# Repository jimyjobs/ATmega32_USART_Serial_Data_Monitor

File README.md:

# ATmega32 USART Serial Data Monitor System

## Overview

This project was completed for CT_321_PBL_04 as an exercise in serial communication using the ATmega32 microcontroller.

The idea behind the project was simple: monitor the state of multiple push buttons and report their status through a USART connection. In addition to transmitting data, the microcontroller was also required to receive commands from a serial terminal and respond appropriately.

The project started with a SimulIDE prototype to verify the firmware logic before moving to schematic capture and PCB design in KiCad.

## Development Process

The firmware was written in C using MPLAB XC8. USART communication was configured for 9600 baud at an 8 MHz system clock. Three push buttons were connected as digital inputs and two LEDs were used to provide visual feedback during operation.

Once the firmware was working correctly in simulation, a custom PCB was designed in KiCad. The design includes:

* ATmega32 DIP package
* 8 MHz crystal oscillator
* Crystal load capacitors
* Decoupling capacitors
* Three push-button inputs
* Two indicator LEDs
* USART header for serial communication

After routing was completed, the board was checked using KiCad's Design Rule Checker (DRC) and all reported issues were resolved before generating the manufacturing files.

## Functional Testing

Testing was performed in SimulIDE using the SerialTerm-32 terminal.

### Switch Monitoring

Each switch press generated the expected message on the serial terminal.

Example:

SW1 PRESSED

SW2 PRESSED

SW3 PRESSED

### Echo Function

To verify bidirectional communication, text entered into the serial terminal was echoed back by the microcontroller.

Example:

Input:
hello

Output:
hello

### STATUS Command

A STATUS command was added to display the current state of the monitored switches.

Example response:

SW1=0

SW2=0

SW3=0

### LED Behaviour

One LED was used as a status indicator while the second LED was used to acknowledge valid command processing. During testing both LEDs behaved as expected.

## PCB Verification

Before generating the fabrication files, the PCB was checked using KiCad verification tools.

Final verification results:

* No ERC errors
* No DRC violations
* No unrouted nets
* Gerber files generated successfully
* Drill files generated successfully

The board was also reviewed using KiCad's 3D Viewer to confirm component placement and overall appearance.

## What I Learned

Through this project I gained practical experience with:

* USART initialization and configuration
* Serial communication debugging
* Command-based firmware design
* PCB layout and routing
* Gerber generation for manufacturing
* Verification using ERC and DRC tools

## Conclusion

The final system met all project requirements. The ATmega32 successfully transmitted switch events, received serial commands, and provided visual feedback through LEDs. Both the firmware and PCB design were verified through simulation and design checks, resulting in a complete and manufacturable embedded system project.

## GROUP MEMBERS
1. NASANIA MSENGI    T23-03-00262
2. NERUSIGWE PATRICK      T23-03-17871
3. JIM JOB           T23-03-11228
4. STEPHEN SAMWEL    T23-03-01246

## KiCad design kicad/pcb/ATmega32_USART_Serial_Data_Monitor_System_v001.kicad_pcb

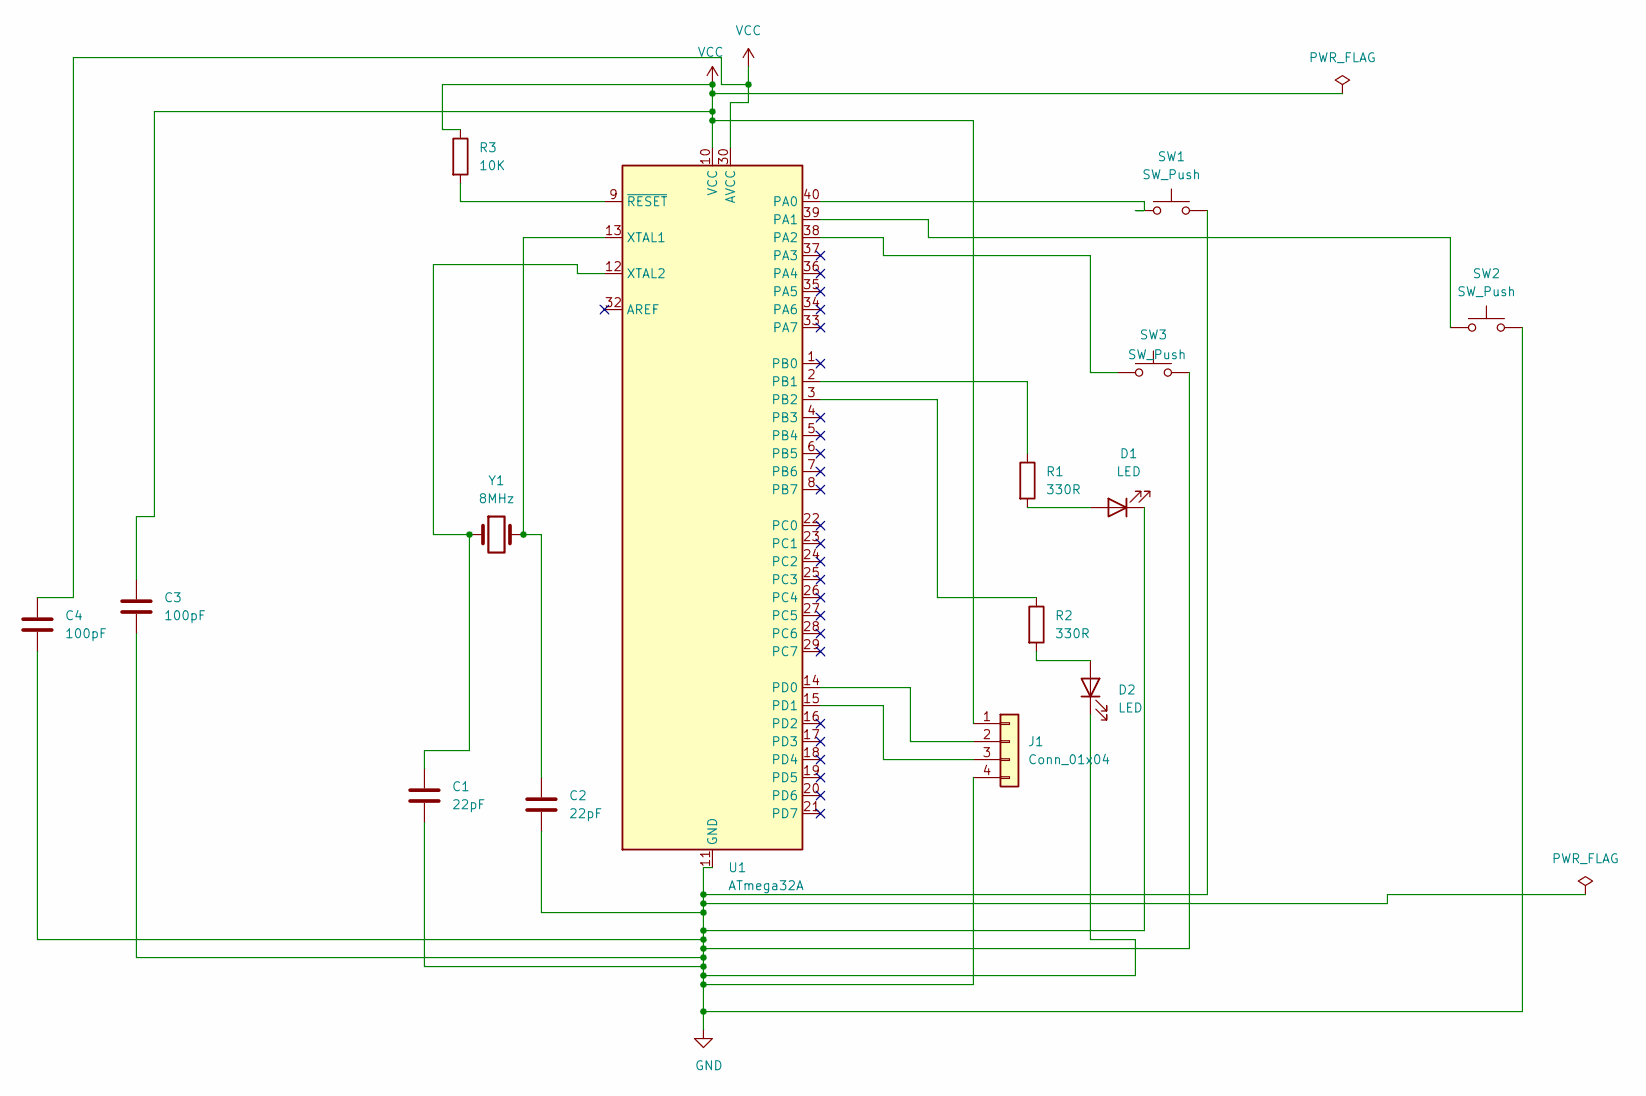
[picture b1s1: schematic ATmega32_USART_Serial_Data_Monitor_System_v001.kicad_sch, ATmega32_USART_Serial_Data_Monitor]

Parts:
C1, C2: 22pF; C_Disc_D5.0mm_W2.5mm_P5.00mm
C3, C4: 100pF; C_Disc_D5.0mm_W2.5mm_P5.00mm
D1, D2: LED; LED_D5.0mm
J1: Conn_01x04; PinHeader_1x04_P2.54mm_Vertical
R1, R2: 330R; R_Axial_DIN0207_L6.3mm_D2.5mm_P7.62mm_Horizontal
R3: 10K; R_Axial_DIN0207_L6.3mm_D2.5mm_P7.62mm_Horizontal
SW1, SW2, SW3: SW_Push; SW_PUSH_6mm
U1: ATmega32A; DIP-40_W15.24mm
Y1: 8MHz; Crystal_HC49-U_Vertical

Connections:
GND: C1.2, C2.2, C3.2, C4.2, D1.1 (K), D2.1 (K), J1.4, SW1.2, SW2.2, SW3.2, U1.11 (GND), U1.31 (GND); also elsewhere on the board
unnamed: D1.2 (A), R1.2
unnamed: D2.2 (A), R2.2
unnamed 3: U1.24 (PC2); also elsewhere on the board
unnamed 4: U1.25 (PC3); also elsewhere on the board
unnamed 5: U1.26 (PC4); also elsewhere on the board
unnamed 6: U1.27 (PC5); also elsewhere on the board
unnamed 7: U1.23 (PC1); also elsewhere on the board
unnamed 8: U1.22 (PC0); also elsewhere on the board
unnamed: J1.2, U1.14 (PD0)
unnamed: J1.3, U1.15 (PD1)
unnamed: SW1.1, U1.40 (PA0)
unnamed: SW2.1, U1.39 (PA1)
unnamed: SW3.1, U1.38 (PA2)
unnamed: R1.1, U1.2 (PB1)
unnamed: R2.1, U1.3 (PB2)
unnamed: C2.1, U1.13 (XTAL1), Y1.2
unnamed: C1.1, U1.12 (XTAL2), Y1.1
unnamed: R3.2, U1.9 (~RESET)
VCC: C3.1, C4.1, J1.1, R3.1, U1.10 (VCC), U1.30 (AVCC); also elsewhere on the board

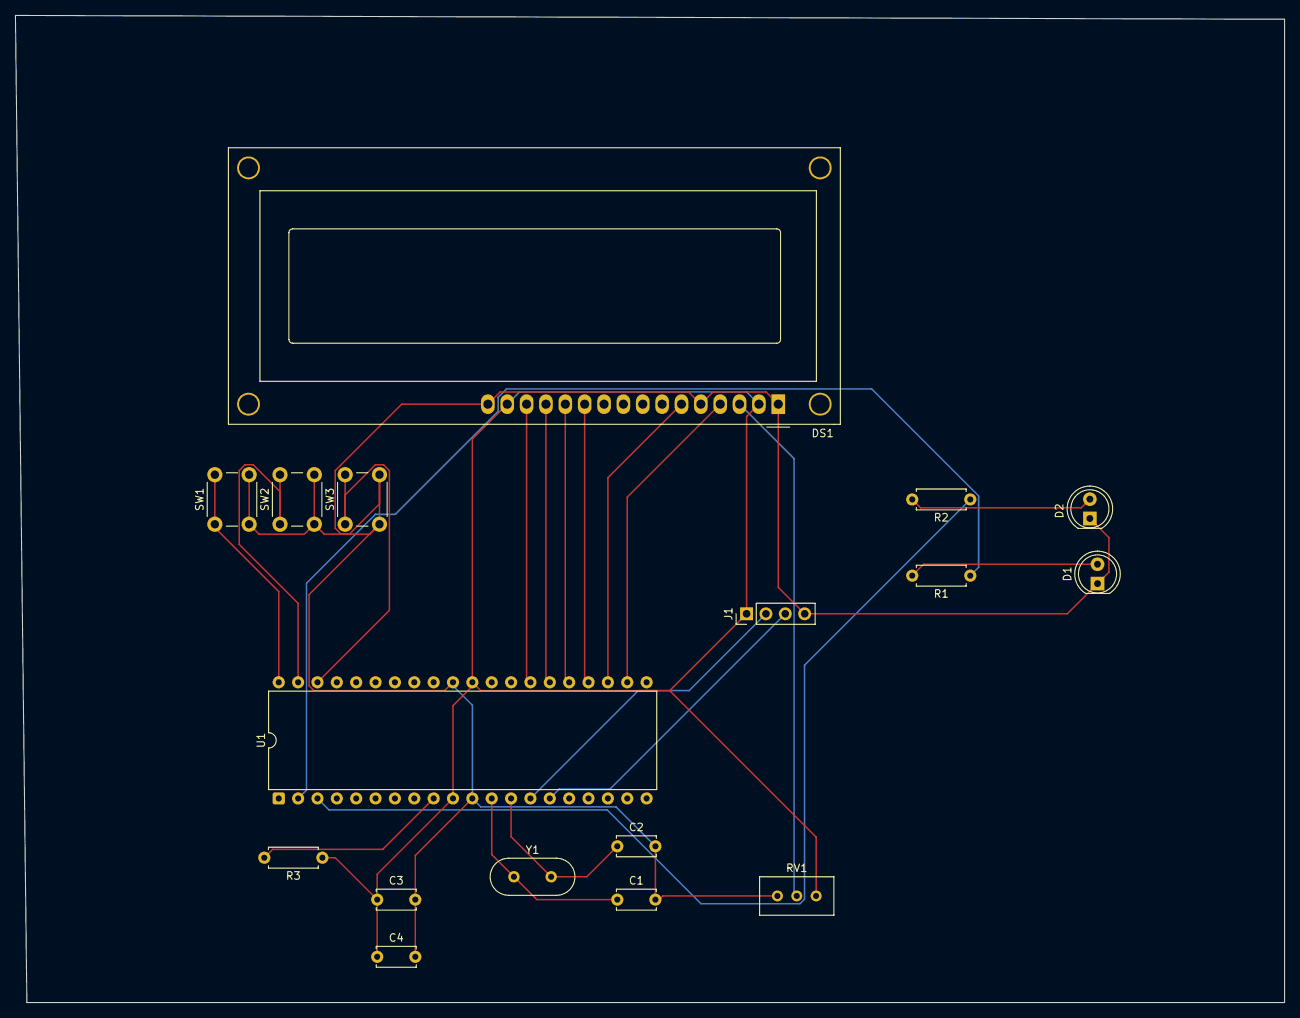
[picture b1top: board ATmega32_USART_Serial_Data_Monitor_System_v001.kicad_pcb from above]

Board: 2 copper layers, 166.5 x 129.5 mm, 17 parts (0 on the bottom side), 21 nets.

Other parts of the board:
DS1: WC1602A
RV1: R_Potentiometer; Potentiometer_Bourns_3296W_Vertical

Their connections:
GND: DS1.1 (VSS), DS1.5 (R/W), DS1.16 (LED(-)), RV1.3; also elsewhere on the board
unnamed 3: DS1.11 (D4); also elsewhere on the board
unnamed 4: DS1.12 (D5); also elsewhere on the board
unnamed 5: DS1.13 (D6); also elsewhere on the board
unnamed 6: DS1.14 (D7); also elsewhere on the board
unnamed 7: DS1.6 (E); also elsewhere on the board
unnamed 8: DS1.4 (RS); also elsewhere on the board
unnamed: DS1.3 (VO), RV1.2
VCC: DS1.2 (VDD), DS1.15 (LED(+)), RV1.1; also elsewhere on the board

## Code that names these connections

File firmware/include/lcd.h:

#ifndef LCD_H
#define LCD_H

#include <avr/io.h>

/* LCD Control Pins */
#define LCD_RS PC0
#define LCD_RW PC1
#define LCD_EN PC2

/* LCD Data Pins */
#define LCD_D4 PC3
#define LCD_D5 PC4
#define LCD_D6 PC5
#define LCD_D7 PC6

/* Function Prototypes */

void LCD_Init(void);

void LCD_Command(unsigned char cmd);

void LCD_Char(unsigned char data);

void LCD_String(const char *str);

void LCD_Clear(void);

void LCD_SetCursor(unsigned char row, unsigned char col);

#endif

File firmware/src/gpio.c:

#define F_CPU 8000000UL
#include <avr/io.h>
#include <util/delay.h>

#include "../include/gpio.h"


void GPIO_Init(void)
{
    /* Configure Switches as Inputs */
    DDRA &= ~((1<<PA0) | (1<<PA1) | (1<<PA2));

    /* Enable Internal Pull-up Resistors */
    PORTA |= (1<<PA0) | (1<<PA1) | (1<<PA2);

    /* Configure LEDs as Outputs */
    DDRB |= (1<<PB1) | (1<<PB2);

    /* Status LED ON */
    PORTB |= (1<<PB1);

    /* Command LED OFF */
    PORTB &= ~(1<<PB2);
}

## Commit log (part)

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2026-06-16 second commit
2026-06-16 third commit
2026-06-17 Rename pin_mapping_table (2).md to pin_mapping_table.md
2026-06-18 Rename test_results[1].md to test_results.md
2026-06-18 New Changes
